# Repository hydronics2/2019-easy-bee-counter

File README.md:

# 2019 Easy Bee Counter V.1

This version of the bee counter is easy to solder and assemble (all through-hole).  It's been tested and works* with sample code provided.

The current tested design is easy to program and approachable to beginner programmers.  The printed circuit board accepts multiple Arduino platforms made by Adafruit including their line of [Adafruit Feather](https://www.adafruit.com/category/777) type micro-controllers and [Adafruit ItsyBitsy](https://www.adafruit.com/category/1008) micro-controllers.   The Adafruit feathers include wifi and long range radio features (*~~esp8266~~, esp32, and **LoRA). All the ItsyBitsy 3V models (M0, M4, and 32u4) should work fine.

*the esp8266 is missing A5 so you have to jumper to another pin
**see below issue with SPI

### [Data Analysis - *why count bees?](https://github.com/hydronics2/2019-easy-bee-counter/blob/master/Data/README.md)
### [Instructions](https://github.com/hydronics2/2019-easy-bee-counter/blob/master/instructions/README.md)
### [Arduino Code](https://github.com/hydronics2/2019-easy-bee-counter/blob/master/arduino/README.md)
### Major Differences/Improvements
- All through-hole components for easy soldering
- Dual footprint, socketed, off-the-shelf micro-controllers => Feather and ItsyBitsy
- Program in Arduino, Lua, and microPython
- A total of 24 gates, 48 sensors, 6 shift registers
- ~14.75" long stretching the entire opening of a langstroth hive for easy placement
- using 2 PCBs to create a sandwich is an inexpensive quick solution. The PCBs must be ordered [black](https://github.com/hydronics2/2019-easy-bee-counter/tree/master/instructions/ordering_instructions) so the IR LED emitter is absorbed into the material.
- using 6 pin headers to create the turn-styles or gates
- N-Ch mosfet controlled IR LEDs such that LEDs can be controlled ON for short periods during while sensing (~75us). Allows for reduced power to less than 1ma (plus micro-controller).

### General Operation
Honeybees are forced through 24 gates where optical sensors (48 sensors) determine whether the bee is present and determine the direction of the bee movement. Each optical sensors has an IR LED and an IR sensor. If no bee is present the IR light is absorbed into the black surface. If a bee is present the IR light reflects off the bee and triggers the sensor. 

### Micro-Controller Pinout
#### Feather ESP32 Pinout

#### ItsyBitsy Pinout

### Shift-in registers
There are 6 shift-in registers. Here's a great description for how to connect and program [shift registers](http://www.gammon.com.au/forum/?id=11979).  The micro-controller's SPI pins read the shift registers. All six shift registers are read at the same time. The sensors are normally pulled low and show 3.3V or HIGH when a transistor is triggered and a bee is present.

Unfortunately the shift registers we're using (the most popular shift register chip!) are not [full SPI devices](https://electronics.stackexchange.com/questions/121249/how-to-put-a-74hc165-on-an-spi-bus) and wont share the SPI with other devices.. They're like the worst SPI devices!... therefore some boards like the Adalogger or LoRa just wont work out of the box. You can still do it by cutting some traces and patching the SPI lines to free pins and bitbanging the SPI to the shift registers.. buy yeah not optimum. You can get a true-spi shift register but the pinout will be different than the 74hc165 used here.

### IR LEDs
The 48 LEDs are divided into two sets of 24 with each set controlled by an N-ch mosfet. The normal forward voltage of each IR LED is 1.2V and about 20ma as shown on the [data sheet](https://www.sparkfun.com/datasheets/Robotics/QR_QRE1113.GR.pdf). Two LEDs are connected in series with a 22ohm resistor. There are jumpers on the board that allow the LEDs to bypass the current limiting resistors. Do not solder the jumper until fully tested! Refer to [these instructions](https://github.com/hydronics2/2019-easy-bee-counter/tree/master/instructions)

### Power
The PCB design connects the USB power pin from the uController to the 3.3V regulator so that a usb cable connected to the micro-controller can power the entire project.

### Bill of Materials
#### uController
The code was tested with the feather esp32 Huzzah and itsyBitsy M0 but will work with all these boards.
- feather Huzzah from [mouser](https://www.mouser.com/ProductDetail/485-3591)
- feather esp8266 from [mouser](https://www.mouser.com/ProductDetail/485-2821)
  - the esp8266 is missing A5, so if this micro is used you have to jumper to another pin
- feather LoRa 900mhz from [mouser](https://www.mouser.com/ProductDetail/485-3178)
- ItsyBitsy M0 from [mouser](https://www.mouser.com/ProductDetail/485-3727)
- ItsyBitsy M4 from [mouser](https://www.mouser.com/ProductDetail/485-3800)
#### PCB
[JLCPCB](https://jlcpcb.com/quote#/) ~$16-25 with shipping. Order the PCBs Black. See [these instructions](https://github.com/hydronics2/2019-easy-bee-counter/tree/master/instructions/ordering_instructions) for ordering.
#### Parts and Pieces from [mouser](https://www.mouser.com/ProjectManager/ProjectDetail.aspx?AccessID=054286973a)
See alternative pricing below for cheaper options specifically for the reflectance sensors.
- [qre1113 Reflective Sensors](https://www.mouser.com/ProductDetail/512-QRE1113f) qty(48)
- [6 pin female headers](https://www.mouser.com/ProductDetail/437-8018700610001101) 7mm high, 0.1" spacing, qty(~36)
- [22ohm resistors](https://www.mouser.com/ProductDetail/Xicon/266-22-RC?qs=sGAEpiMZZMvrmc6UYKmaNXFefT4dxyTCwtpTxTI0yoo%3D), bussed, qty(4)
SIP Packaged, bussed
- [100k ohm resistors](https://www.mouser.com/ProductDetail/IRC-TT-Electronics/L091S104LF?qs=sGAEpiMZZMvrmc6UYKmaNdnTrsZX%2FuSiyGduauH5Qpc%3D) bussed, qty(6)
SIP-9, 8 resistors, 9 pins
- Shift registers, qty(6)
[74HC165](https://www.mouser.com/ProductDetail/595-SN74HC165N)
- [3.3V Regulator](https://www.mouser.com/ProductDetail/Microchip-Technology/MCP1826S-3302E-AB?qs=sGAEpiMZZMsGz1a6aV8DcJ7KfjtCj7Xd5CqQpyOghgk%3D), (input, ground, output - IGO, pinout), qty(1)
- [screw terminals](https://www.mouser.com/ProductDetail/490-TB006-508-02BE) Two pin, 0.1", qty(3)
- [0.1 uF Ceramic Capacitor](https://www.mouser.com/ProductDetail/594-K104K15X7RF53H5), through hole, qty(6)
- [1 uF Ceramic Capacitor](https://www.mouser.com/ProductDetail/594-K105Z20Y5VF5TL2), through hole, qty(1)
- [560uF, 6.3V Capacitor](https://www.mouser.com/ProductDetail/661-APSC6R3L561MH08S)
low esr, 3.5mm lead spacing, 8mm diameter
- N-Channel Mosfet [FQP30N06](https://www.mouser.com/ProductDetail/512-FQP30N06L), qty(2)
  - [chinswain](https://github.com/hydronics2/2019-easy-bee-counter/issues/20#issuecomment-2094117078) suggested using this IRLB8721PbF N-Channel mosfet. He suggested the signal threshold of 3.3V was not sufficient to meet the gate threshold for the FQP30N06L... and it could be the ebay versions of the FQP30N06L floating around are not to spec.

#### Alternative pricing from Chinese distributor LCSC
Someone pointed out some alternative pricing that can really bring the cost down.
- [ITR8307 Reflectance Sensors](https://lcsc.com/product-detail/Photo-Interrupter_Everlight-Elec-ITR8307_C63451.html) ~$0.13/each @ qty(48) (same as QRE1113)
- [6 pin female headers](https://lcsc.com/product-detail/Pin-Header-Female-Header_BOOMELE-Boom-Precision-Elec-C40877_C40877.html) 8.5mm high. ~$0.05/each @ qty(36+)
- [22 ohm SIP](https://lcsc.com/product-detail/Resistor-Networks-Arrays_FH-Guangdong-Fenghua-Advanced-Tech-A09-220JP_C9105.html) 8 resistor, 9 pin, it will fit. $0.44 for qty(4)
- [100k SIP Resistors](https://lcsc.com/product-detail/Resistor-Networks-Arrays_FH-Guangdong-Fenghua-Advanced-Tech-A09-104JP_C9108.html) 8 resistor, 9pin, it will fit. $0.44 for qty(6)

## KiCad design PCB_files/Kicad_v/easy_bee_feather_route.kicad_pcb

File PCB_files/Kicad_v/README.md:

The GERBER files were developed from the kicad board files and there was a small error in the kiCAD files... so the gerber files have been removed. You now have to use the Eagle board files or generate gerber files from the eagle board files.... or a lot of PCB manufacturers will take eagle PCB files and you don't have to generate your own gerber files. You can still use the kicad files but you have to route a small trace for the SCK pin. See this bug report: https://github.com/hydronics2/2019-easy-bee-counter/issues/25

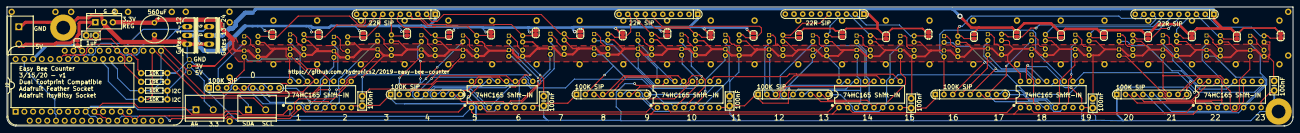
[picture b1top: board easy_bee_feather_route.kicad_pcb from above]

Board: 2 copper layers, 373.4 x 34.5 mm, 145 parts (0 on the bottom side), 115 nets.

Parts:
C1, C2, C3, C4, C5, C6: 0.1uF; CAP-PTH-SMALL-KIT
C7: 1uF; CAP-PTH-SMALL-KIT
C8: 560uF; E3,5-8
J1, J3, J4: CONN_025MM; SCREWTERMINAL-5MM-2
J2: ItsyBitsy_M0_M4; DIP-28_W15.24mm
JP1: JUMPER-SMT_2_NC_TRACE_SILK; SMT-JUMPER_2_NC_TRACE_SILK
JP2, JP3, JP4, JP5, JP6, JP7, JP8, JP9, JP10, JP11, JP12, JP13, JP14, JP15, JP16, JP17, JP18, JP19, JP20, JP21, JP22, JP23, JP24, JP25: SolderJumper_2_Open; SolderJumper-2_P1.3mm_Open_RoundedPad1.0x1.5mm
MS2: FEATHERWING_NODIM; FEATHERWING_DIM
Q6, Q7: 60V/32A/35mΩ; TO220V
R1, R3, R4, R13: 10k; AXIAL-0.3
R2, R5, R6, R7, R11, R12: RPACK-BUSSED-8-SIP-PTH-8; RPACK-SIP-PTH-8
S1, S2: STANDOFF_ELECTRICAL5-32; STANDOFF_ELECTRICAL_5_32
U1, U2, U3, U4, U5, U6: 74165; DIP16
U7: V_REG_78XXSINK; TO220-IGO
U$1, U$2, U$3, U$4, U$5, U$6, U$7, U$8, U$9, U$10, U$11, U$12, U$13, U$14, U$15, U$16, U$17, U$18, U$19, U$20, U$21, U$22, U$23, U$24, U$25, U$26, U$27, U$28, U$29, U$30, U$59: M06_BEE; 1X06_BEE
U$31, U$39, U$40: CONN_0138MILL; 1X01-40MILL
U$34, U$35, U$36, U$37: RPACK-BUSSED-9; RPACK-SIP-PTH-9
U$68, U$69, U$70, U$71, U$72, U$73, U$74, U$75, U$76, U$77, U$78, U$79, U$80, U$81, U$82, U$83, U$84, U$85, U$86, U$87, U$88, U$89, U$90, U$91, U$92, U$93, U$94, U$95, U$96, U$97, U$98, U$99, U$100, U$101, U$102, U$103, U$104, U$105, U$106, U$107, U$108, U$109, U$110, U$111, U$112, U$113, U$114, U$115: QRE1113_; DIP400W50P180L360H200Q4

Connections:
3.3V: C1.1, C2.1, C3.1, C4.1, C5.1, C6.1, C8.+, J3.2, R1.P$2, R3.P$2, U1.16, U2.16, U3.16, U4.16, U5.16, U6.16, U7.OUT, U$39.1, U$68.1, U$68.3, U$69.3, U$70.1, U$70.3, U$71.3, U$72.1, U$72.3, U$73.3, U$74.1, U$74.3, U$75.3, U$76.1, U$76.3, U$77.3, U$78.1, U$78.3, U$79.3, U$80.1, U$80.3, U$81.3, U$82.1, U$82.3, U$83.3, U$84.1, U$84.3, U$85.3, U$86.1, U$86.3, U$87.3, U$88.1, U$88.3, U$89.3, U$90.1, U$90.3, U$91.3, U$92.1, U$92.3, U$93.3, U$94.1, U$94.3, U$95.3, U$96.1, U$96.3, U$97.3, U$98.1, U$98.3, U$99.3, U$100.1, U$100.3, U$101.3, U$102.1, U$102.3, U$103.3, U$104.1, U$104.3, U$105.3, U$106.1, U$106.3, U$107.3, U$108.1, U$108.3, U$109.3, U$110.1, U$110.3, U$111.3, U$112.1, U$112.3, U$113.3, U$114.1, U$114.3, U$115.3
5V: C7.1, J1.2, JP1.1, U7.IN, U$40.1
/1_CATHODE: JP2.1, U$36.P$9, U$115.2
/2_CATHODE: JP3.1, U$36.P$8, U$113.2
/3_CATHODE: JP4.1, U$36.P$7, U$111.2
/4_CATHODE: JP5.1, U$36.P$6, U$109.2
/5_CATHODE: JP6.1, U$36.P$5, U$107.2
/6_CATHODE: JP7.1, U$36.P$4, U$105.2
/7_CATHODE: JP8.1, U$36.P$3, U$103.2
/8_CATHODE: JP9.1, U$36.P$2, U$101.2
/9_CATHODE: JP25.2, U$37.P$9, U$99.2
/10_CATHODE: JP24.2, U$37.P$8, U$97.2
/11_CATHODE: JP23.2, U$37.P$7, U$95.2
/12_CATHODE: JP22.2, U$37.P$6, U$93.2
/13_CATHODE: JP21.2, U$35.P$5, U$91.2
/14_CATHODE: JP20.2, U$35.P$4, U$89.2
/15_CATHODE: JP19.2, U$35.P$3, U$87.2
/16_CATHODE: JP18.2, U$35.P$2, U$85.2
/17_CATHODE: JP17.2, U$34.P$9, U$83.2
/18_CATHODE: JP16.2, U$34.P$8, U$81.2
/19_CATHODE: JP15.2, U$34.P$7, U$79.2
/20_CATHODE: JP14.2, U$34.P$6, U$77.2
/21_CATHODE: JP13.2, U$34.P$5, U$75.2
/22_CATHODE: JP12.2, U$34.P$4, U$73.2
/23_CATHODE: JP11.2, U$34.P$3, U$71.2
/24_CATHODE: JP10.2, U$34.P$2, U$69.2
/A4: J2.9, J3.1, MS2.9
/LOAD: J2.10, MS2.10, U1.1, U2.1, U3.1, U4.1, U5.1, U6.1
/MISO: J2.13, MS2.13, U6.9
/P1: J2.22, MS2.21, Q7.1, R4.P$2
/P2: J2.23, MS2.22, Q6.1, R13.P$2
/SCK: MS2.11, U1.2, U2.2, U3.2, U4.2, U5.2, U6.2
/SCL: J2.18, J4.2, MS2.18, R3.P$1
/SDA: J2.17, J4.1, MS2.17, R1.P$1
/SER1: U5.9, U6.10
/SER2: U4.9, U5.10
/SER3: U2.9, U3.10
/SER4: U1.9, U2.10
/USB: J2.26, JP1.2, MS2.26
GND: C1.2, C2.2, C3.2, C4.2, C5.2, C6.2, C7.2, C8.-, J1.1, J2.27, MS2.4, Q6.3, Q7.3, R2.P$1, R4.P$1, R5.P$1, R6.P$1, R7.P$1, R11.P$1, R12.P$1, R13.P$1, S1.P1, S2.P1, U1.8, U1.15, U2.8, U2.15, U3.8, U3.15, U4.8, U4.15, U5.8, U5.15, U6.8, U6.15, U7.GND, U$31.1
unnamed: JP2.2, JP3.2, JP4.2, JP5.2, JP6.2, JP7.2, JP8.2, JP9.2, JP22.1, JP23.1, JP24.1, JP25.1, Q7.2, U$36.P$1, U$37.P$1
unnamed: JP10.1, JP11.1, JP12.1, JP13.1, JP14.1, JP15.1, JP16.1, JP17.1, JP18.1, JP19.1, JP20.1, JP21.1, Q6.2, U$34.P$1, U$35.P$1
unnamed: R2.P$2, U1.3, U$70.4
unnamed: R2.P$3, U1.4, U$71.4
unnamed: R2.P$4, U1.6, U$69.4
unnamed: R2.P$5, U1.5, U$68.4
unnamed: R2.P$6, U1.14, U$73.4
unnamed: R2.P$7, U1.13, U$72.4
unnamed: R2.P$8, U1.12, U$75.4
unnamed: R2.P$9, U1.11, U$74.4
unnamed: R5.P$2, U2.11, U$82.4
unnamed: R5.P$3, U2.12, U$83.4
unnamed: R5.P$4, U2.13, U$80.4
unnamed: R5.P$5, U2.14, U$81.4
unnamed: R5.P$6, U2.3, U$78.4
unnamed: R5.P$7, U2.4, U$79.4
unnamed: R5.P$8, U2.5, U$76.4
unnamed: R5.P$9, U2.6, U$77.4
unnamed: R6.P$2, U3.12, U$91.4
unnamed: R6.P$3, U3.11, U$90.4
unnamed: R6.P$4, U3.13, U$88.4
unnamed: R6.P$5, U3.14, U$89.4
unnamed: R6.P$6, U3.3, U$86.4
unnamed: R6.P$7, U3.4, U$87.4
unnamed: R6.P$8, U3.5, U$84.4
unnamed: R6.P$9, U3.6, U$85.4
unnamed: R7.P$2, U4.11, U$98.4
unnamed: R7.P$3, U4.12, U$99.4
unnamed: R7.P$4, U4.13, U$96.4
unnamed: R7.P$5, U4.14, U$97.4
unnamed: R7.P$6, U4.3, U$94.4
unnamed: R7.P$7, U4.4, U$95.4
unnamed: R7.P$8, U4.5, U$92.4
unnamed: R7.P$9, U4.6, U$93.4
unnamed: R11.P$2, U5.11, U$106.4
unnamed: R11.P$3, U5.12, U$107.4
unnamed: R11.P$4, U5.13, U$104.4
unnamed: R11.P$5, U5.14, U$105.4
unnamed: R11.P$6, U5.3, U$102.4
unnamed: R11.P$7, U5.4, U$103.4
unnamed: R11.P$8, U5.5, U$100.4
unnamed: R11.P$9, U5.6, U$101.4
unnamed: R12.P$2, U6.12, U$115.4
unnamed: R12.P$3, U6.11, U$114.4
unnamed: R12.P$4, U6.13, U$112.4
unnamed: R12.P$5, U6.14, U$113.4
unnamed: R12.P$6, U6.3, U$110.4
unnamed: R12.P$7, U6.4, U$111.4
unnamed: R12.P$8, U6.5, U$108.4
unnamed: R12.P$9, U6.6, U$109.4
unnamed: U3.9, U4.10
unnamed: U$68.2, U$69.1
unnamed: U$70.2, U$71.1
unnamed: U$72.2, U$73.1
unnamed: U$74.2, U$75.1
unnamed: U$76.2, U$77.1
unnamed: U$78.2, U$79.1
unnamed: U$80.2, U$81.1
unnamed: U$82.2, U$83.1
unnamed: U$84.2, U$85.1
unnamed: U$86.2, U$87.1
unnamed: U$88.2, U$89.1
unnamed: U$90.2, U$91.1
unnamed: U$92.2, U$93.1
unnamed: U$94.2, U$95.1
unnamed: U$96.2, U$97.1
unnamed: U$98.2, U$99.1
unnamed: U$100.2, U$101.1
unnamed: U$102.2, U$103.1
unnamed: U$104.2, U$105.1
unnamed: U$106.2, U$107.1
unnamed: U$108.2, U$109.1
unnamed: U$110.2, U$111.1
unnamed: U$112.2, U$113.1
unnamed: U$114.2, U$115.1

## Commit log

2019-12-15 Create description
2020-02-22 updated SIP 22ohm resistors to qty(4)
2020-02-22 updated shift register link to quantities small
2020-02-22 update part quantities
2020-03-14 not_sure
2020-03-15 version1
    updated with version 1 Feather only and kicad design files
2020-03-15 add video
2020-03-15 udpates
2020-03-15 updated instructions
2020-03-15 still working on PCB files
2020-03-15 new gerber view
2020-03-15 update pics
2020-03-15 add data
2020-03-15 data
2020-03-16 readme updates
2020-03-16 updated code with itsybitsy power pins
2020-03-16 add gerbers
2020-03-16 update readmes'
2020-03-17 updated blinking IR leds
2020-03-17 new pic
2020-03-17 add instructions video
2020-03-23 Converted Bee Logo into an Eagle Part
    Here's a library containing a single device which has 1 symbol and 1 package.
    The symbol is a simple rectangle that shows up in the schematic and says "Bee Logo".
    Adding the device in the schematic editor will create a copy of the image in the schematic which can be grabbed by the Anchor at the lower left corner and easily moved around for placement on the PCB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
    The Bee Logo itself is in the TPlace layer (as was the original Bee Logo). The anchor for dragging it around is in the Reference layer so that the anchor doesn't get printed on the actual silk screen.
    Mirroring the logo will automatically move it to the BPlace layer as well.
2020-03-23 SN74HC165N
2020-03-23 added info
2020-03-30 Converted Logo to library part Added vias to be solded bridged for jumpers to bypass the SIP resistors. Rerouted the board, realigned many of the parts.
2020-03-30 Added jumpers for 13-24 (oops). Added Tkeepout areas to expose jumpers on component side.
2020-03-30 cleaned up some additional errors.
2020-04-25 removed chipselect pins in bee-counter code
2020-04-25 added kiCad_files
2020-04-25 added gerbers
2020-04-26 updated gerber files
2020-04-26 re-uploaded the gerbers
    the last zip file was corrupt for some reason
2020-04-28 updated gerber download instructions
2020-05-01 removed a duplicate file
2020-05-01 re-output gerber files
    JLCPCB indicated in an email that something was wrong with the gerber files. Seemed to upload fine. OSHPark said they were missing the copper layer which was strange.. Re-output gerber files based on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
2020-05-05 Create featherhuzzah_bee_counter_WiFi
2020-05-05 Update featherhuzzah_bee_counter_WiFi
2020-05-06 Create easy_bee_counter.lbr
    added libraries from ULP export from eagle file
2020-05-08 Reworked connections to 74*165s to put the sense pins in a better order for the board layout.
2020-05-11 Finalized all connections on schematic (missed some sensors last commit). Fully routed board using new component names and new pinouts for SIP packs.
2020-05-11 Corrected unusable pins for servos
2020-05-11 Improvements to test_shift_registers.ino Works with new serial pinout Optimized code quite a bit, removed repetitive code. Added ability to remap serial pinout by editing simple binary array. Set up 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
2020-05-11 Improved clarity in documentation at beginning of file.
2020-05-12 Ported to new pin map Optimized code similarly to previous efforts on test_shift_registers sketch I believe there are other opportunities for optimization, but this took care of the low hanging fruit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
2020-05-12 Added conditional compile for board rev
2020-05-20 note on using the esp8266
    pin A5 is missing!
2020-07-21 added python sample code
2020-08-01 added the detail that the LoRa module
    the LoRa module also requires SPI so you need true SPI chips with the LoRa.
2021-03-01 Update README.md
    updated the readMe detailing issues with the 74HC165 not being a true SPI device
2024-03-07 Update README.MD
    The GERBER files were developed from the kicad board files so had to remove the gerber files. You now have to use the Eagle board files or generate gerber files from the eagle board files.
    https://github.com/hydronics2/2019-easy-bee-counter/issues/25
2024-03-07 Update README.md
    The GERBER files were developed from the kicad board files so had to remove the gerber files. You now have to use the Eagle board files or generate gerber files from the eagle board files.... or a lo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
2024-03-07 Delete PCB_files/gerbers2.zip
    The GERBER files were developed from the kicad board files and there was a small error in the kiCAD files... so the gerber files have been removed. You now have to use the Eagle board files or genera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
2024-03-07 Delete PCB_files/Kicad_v/gerbers directory
    The GERBER files were developed from the kicad board files and there was a small error in the kiCAD files... so the gerber files have been removed. You now have to use the Eagle board files or genera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
2024-03-07 Create read.me
    There is a small error in the kiCAD files... You now have to use the Eagle board files or generate gerber files from the eagle board files.... or a lot of PCB manufacturers will take eagle PCB files 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
2024-03-07 Create README.md
    see message
2024-05-05 Update README.md
    added alternative N-channel mosfet suggestion IRLB8721PbF.
2024-05-05 Update README.md
    update description of the N-channel mosfet
